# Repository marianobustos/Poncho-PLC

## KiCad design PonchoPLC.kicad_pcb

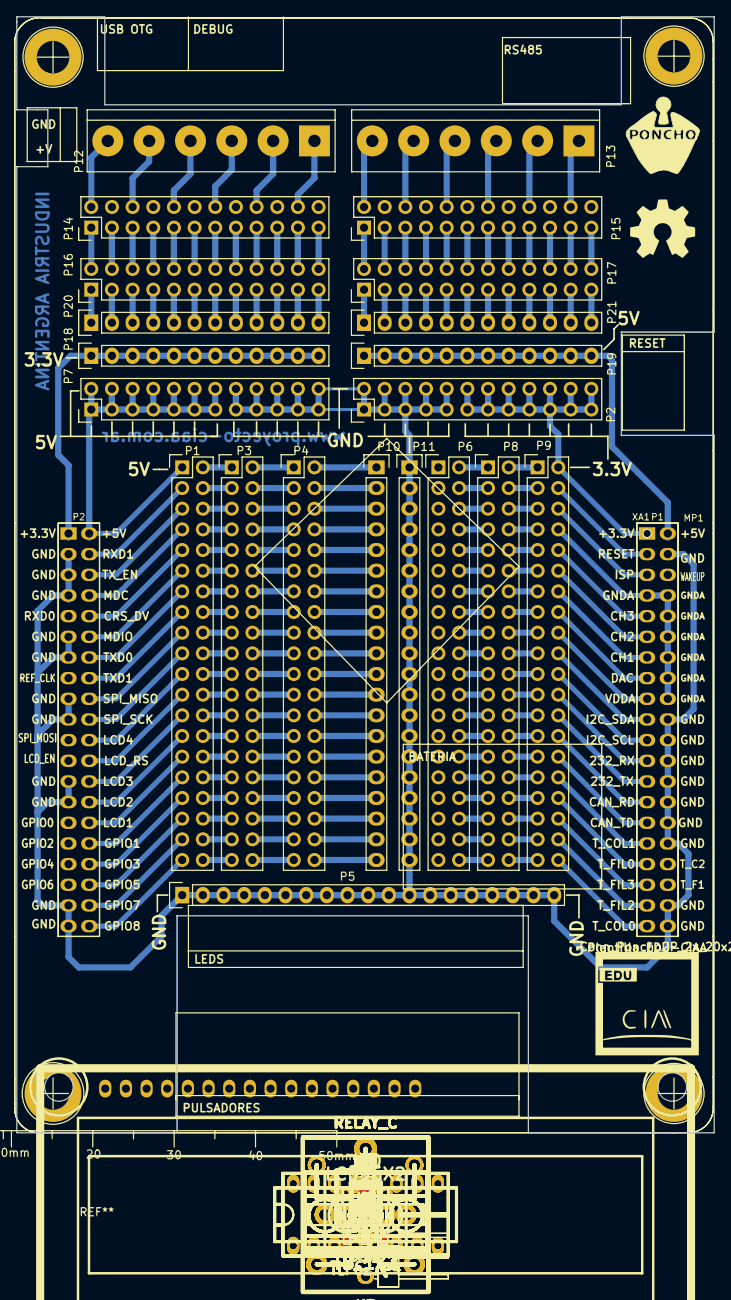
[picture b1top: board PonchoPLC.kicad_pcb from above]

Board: 2 copper layers, 85.7 x 137.2 mm, 135 parts (0 on the bottom side), 253 nets.

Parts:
C1, C2, C3, C4: 100nF; C_1206
C5, C6, C7, C8: 1uF; C_1206
D1, D2, D3, D4, D5, D6, D7, D8, D9, D10, D11, D12, D13, D16, D17: LED red; LED_1206
D14, D15, D18, D19: LL4148; SOD80C
DS1: LCD16X2; LCD_16x2
G101: Logo_OSHWA
J1: I2C; HEADER-4H
J2: RS-232; HEADER-4H
J3, J4, J8, J9, J10, J11: TB_1X3; BORNERA3
J5: TB_1X2; BORNERA2
J6, J7: TB_1X2; BORNERA3
JP1, JP2, JP3, JP4: Jumper; Pin_strip_2
K1, K2, K3, K4: RELAY_C; Relay_C
MP1: Plantilla_EDU-CIAA
P1, P3, P4, P6, P8, P9: CONN_02X20; Pin_Header_Straight_2x20
P2, P7: CONN_01X20; Pin_Header_Straight_2x12
P5: CONN_01X19; Pin_Header_Straight_1x19
P10, P11: CONN_01X20; Pin_Header_Straight_1x20
P12, P13: CONN_01X06; bornier6
P14, P15, P16, P17: CONN_02X12; Pin_Header_Straight_2x12
P18, P19, P20, P21: CONN_01X12; Pin_Header_Straight_1x12
Q1, Q2, Q3, Q4: FQT13N06L; SOT-223
Q5, Q6, Q7, Q8: 2N7002; SOT23
R1: 100; R_1206
R2, R3, R4, R5, R6, R7, R8: 3.3k; R_1206
R9, R10, R11, R12, R13, R14, R15: 4.7k; R_1206
R16, R18, R20, R22, R24, R26, R28: 2.2k; R_1206
R17, R19, R21, R23, R25, R27, R29, R30, R31, R32, R33, R38, R39, R42, R43: 100k; R_1206
R34, R35, R36, R37, R40, R41, R44, R45: 330; R_1206
RV1: 10K; TRIMER_V
TH1, TH2, TH3, TH4: PTS12066V100; PTC_1210
U1, U2: TLP627-4; DIP_16-300_socket
U3, U4, U5, U6: MCP1416; SOT-23-5
XA1: Conn_Poncho2P_2x_20x2; poncho_grande

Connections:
+3.3V: P2.11, P2.12, P2.13, P2.14, P2.15, P2.16, P2.17, P2.18, P2.19, P2.20, P2.21, P2.22, P2.23, P2.24, P9.2
+3.3VADC: P9.18, XA1.17
+3.3VP: P18.1, P18.2, P18.3, P18.4, P18.5, P18.6, P18.7, P18.8, P18.9, P18.10, P18.11, P18.12, XA1.41
+3V3: J1.1, J2.1, R16.2, R17.2, R18.2, R19.2, R20.2, R21.2, R22.2, R23.2, R24.2, R25.2, R26.2, R27.2, R28.2, R29.2, XA1.1
+5V: C1.2, C2.2, C3.2, C4.2, C5.2, C6.2, C7.2, C8.2, D12.1, D13.1, D14.2, D15.2, D16.1, D17.1, D18.2, D19.2, DS1.2, DS1.15, K1.5, K2.5, K3.5, K4.5, P19.1, P19.2, P19.3, P19.4, P19.5, P19.6, P19.7, P19.8, P19.9, P19.10, P19.11, P19.12, RV1.1, U3.2, U4.2, U5.2, U6.2, XA1.2
+5VP: P1.1, P7.1, P7.2, P7.3, P7.4, P7.5, P7.6, P7.7, P7.8, P7.9, P7.10, P7.11, P7.12, P7.13, P7.14, XA1.42
/Conector del Poncho/COL0: D1.2, R17.1, U1.16, XA1.39
/Conector del Poncho/COL1: D2.2, R19.1, U1.14, XA1.31
/Conector del Poncho/COL2: D3.2, R21.1, U1.12, XA1.34
/Conector del Poncho/LCD1: DS1.11, XA1.70
/Conector del Poncho/LCD2: DS1.12, XA1.68
/Conector del Poncho/LCD3: DS1.13, XA1.66
/Conector del Poncho/LCD4: DS1.14, XA1.62
/Conector del Poncho/LCD_EN: DS1.6, XA1.63
/Conector del Poncho/RS: DS1.4, XA1.64
/Conector del Poncho/RXD: J2.2, XA1.23
/Conector del Poncho/SCL: J1.3, XA1.21
/Conector del Poncho/SDA: J1.2, XA1.19
/Conector del Poncho/TXD: J2.3, XA1.25
/Entradas Optoacopladas/COM: J5.2, R9.1, R10.1, R11.1, R12.1, R13.1, R14.1, R15.1, U1.2, U1.4, U1.6, U1.8, U2.2, U2.4, U2.6
/Entradas Optoacopladas/DIN3: D4.2, R23.1, U1.10, XA1.33
/Entradas Optoacopladas/DIN4: D5.2, R25.1, U2.16, XA1.36
/Entradas Optoacopladas/DIN5: D6.2, R27.1, U2.14, XA1.37
/Entradas Optoacopladas/DIN6: D7.2, R29.1, U2.12, XA1.35
/Entradas Optoacopladas/IN0: J3.1, R2.1
/Entradas Optoacopladas/IN1: J3.2, R3.1
/Entradas Optoacopladas/IN2: J3.3, R4.1
/Entradas Optoacopladas/IN3: J4.1, R5.1
/Entradas Optoacopladas/IN4: J4.2, R6.1
/Entradas Optoacopladas/IN5: J4.3, R7.1
/Entradas Optoacopladas/IN6: J5.1, R8.1
/Salidas Digitales/C1A: J8.3, K2.1
/Salidas Digitales/C1B: J9.3, K4.1
/Salidas Digitales/C1C: J10.3, K1.1
/Salidas Digitales/C1D: J11.3, K3.1
/Salidas Digitales/DOUT0: Q6.1, R39.1, XA1.69
/Salidas Digitales/DOUT1: Q8.1, R43.1, XA1.72
/Salidas Digitales/DOUT2: Q5.1, R38.1, XA1.71
/Salidas Digitales/DOUT3: Q7.1, R42.1, XA1.74
/Salidas Digitales/DOUT4: JP2.1, R30.1, U3.3, XA1.73
/Salidas Digitales/DOUT5: JP1.1, R31.1, U4.3, XA1.76
/Salidas Digitales/DOUT6: JP3.1, R32.1, U5.3, XA1.75
/Salidas Digitales/DOUT7: JP4.1, R33.1, U6.3, XA1.78
/Salidas Digitales/MOS4: JP2.2, Q1.1, R34.2, U3.5
/Salidas Digitales/MOS5: JP1.2, Q2.1, R35.2, U4.5
/Salidas Digitales/MOS6: JP3.2, Q3.1, R36.2, U5.5
/Salidas Digitales/MOS7: JP4.2, Q4.1, R37.2, U6.5
/Salidas Digitales/NC1A: J8.1, K2.4
/Salidas Digitales/NC1B: J9.1, K4.4
/Salidas Digitales/NC1C: J10.1, K1.4
/Salidas Digitales/NC1D: J11.1, K3.4
/Salidas Digitales/NO1A: J8.2, K2.3
/Salidas Digitales/NO1B: J9.2, K4.3
/Salidas Digitales/NO1C: J10.2, K1.3
/Salidas Digitales/NO1D: J11.2, K3.3
GND: C1.1, C2.1, C3.1, C4.1, C5.1, C6.1, C7.1, C8.1, D8.2, D9.2, D10.2, D11.2, DS1.1, DS1.5, J1.4, J2.4, P2.1, P2.2, P2.3, P2.4, P2.5, P2.6, P2.7, P2.8, P2.9, P2.10, P5.1, P5.2, P5.3, P5.4, P5.5, P5.6, P5.7, P5.8, P5.9, P5.10, P5.11, P5.12, P5.13, P5.14, P5.15, P5.16, P5.17, P5.18, P5.19, P7.15, P7.16, P7.17, P7.18, P7.19, P7.20, P7.21, P7.22, P7.23, P7.24, P11.1, P11.2, P11.3, P11.4, P11.5, P11.6, P11.7, P11.8, P11.9, P11.10, P11.11, P11.12, P11.13, P11.14, P11.15, P11.16, P11.17, P11.18, P11.19, P11.20, Q1.3, Q2.3, Q3.3, Q4.3, Q5.3, Q6.3, Q7.3, Q8.3, R1.2, R30.2, R31.2, R32.2, R33.2, R38.2, R39.2, R42.2, R43.2, RV1.3, U1.9, U1.11, U1.13, U1.15, U2.11, U2.13, U2.15, U3.4, U4.4, U5.4, U6.4, XA1.4, XA1.20, XA1.22, XA1.24, XA1.26, XA1.28, XA1.30, XA1.32, XA1.38, XA1.40, XA1.43, XA1.45, XA1.47, XA1.51, XA1.53, XA1.57, XA1.59, XA1.65, XA1.67, XA1.77, XA1.79
GNDA: P9.8, XA1.7, XA1.8, XA1.10, XA1.12, XA1.14, XA1.16, XA1.18
unnamed: D1.1, R16.1
unnamed: D2.1, R18.1
unnamed: D3.1, R20.1
unnamed: D4.1, R22.1
unnamed: D5.1, R24.1
unnamed: D6.1, R26.1
unnamed: D7.1, R28.1
unnamed: D8.1, R37.1
unnamed: D9.1, R34.1
unnamed: D10.1, R35.1
unnamed: D11.1, R36.1
unnamed: D12.2, R40.2
unnamed: D13.2, R41.2
unnamed: D14.1, K1.2, Q5.2, R40.1
unnamed: D15.1, K2.2, Q6.2, R41.1
unnamed: D16.2, R44.2
unnamed: D17.2, R45.2
unnamed: D18.1, K3.2, Q7.2, R44.1
unnamed: D19.1, K4.2, Q8.2, R45.1
unnamed: DS1.3, RV1.2
unnamed: DS1.16, R1.1
unnamed: J6.1, TH1.2
unnamed: J6.2, TH2.2
unnamed: J7.1, TH3.2
unnamed: J7.2, TH4.2
unnamed: P1.2, P3.1
unnamed: P1.4, P3.3
unnamed: P1.6, P3.5
unnamed: P1.8, P3.7
unnamed: P1.10, P3.9
unnamed: P1.12, P3.11
unnamed: P1.14, P3.13
unnamed: P1.16, P3.15
unnamed: P1.18, P3.17
unnamed: P1.20, P3.19
unnamed: P1.22, P3.21
unnamed: P1.24, P3.23
unnamed: P1.26, P3.25
unnamed: P1.28, P3.27
unnamed: P1.30, P3.29
unnamed: P1.32, P3.31
unnamed: P1.34, P3.33
unnamed: P1.36, P3.35
unnamed: P1.38, P3.37
unnamed: P1.40, P3.39
unnamed: P3.2, P4.1
unnamed: P3.4, P4.3
unnamed: P3.6, P4.5
unnamed: P3.8, P4.7
unnamed: P3.10, P4.9
unnamed: P3.12, P4.11
unnamed: P3.14, P4.13
unnamed: P3.16, P4.15
unnamed: P3.18, P4.17
unnamed: P3.20, P4.19
unnamed: P3.22, P4.21
unnamed: P3.24, P4.23
unnamed: P3.26, P4.25
unnamed: P3.28, P4.27
unnamed: P3.30, P4.29
unnamed: P3.32, P4.31
unnamed: P3.34, P4.33
unnamed: P3.36, P4.35
unnamed: P3.38, P4.37
unnamed: P3.40, P4.39
unnamed: P6.2, P8.1
unnamed: P6.4, P8.3
unnamed: P6.6, P8.5
unnamed: P6.8, P8.7
unnamed: P6.10, P8.9
unnamed: P6.12, P8.11
unnamed: P6.14, P8.13
unnamed: P6.16, P8.15
unnamed: P6.18, P8.17
unnamed: P6.20, P8.19
unnamed: P6.22, P8.21
unnamed: P6.24, P8.23
unnamed: P6.26, P8.25
unnamed: P6.28, P8.27
unnamed: P6.30, P8.29
unnamed: P6.32, P8.31
unnamed: P6.34, P8.33
unnamed: P6.36, P8.35
unnamed: P6.38, P8.37
unnamed: P6.40, P8.39
unnamed: P8.2, P9.1
unnamed: P8.4, P9.3
unnamed: P8.6, P9.5
unnamed: P8.8, P9.7
unnamed: P8.10, P9.9
unnamed: P8.12, P9.11
unnamed: P8.14, P9.13
unnamed: P8.16, P9.15
unnamed: P8.18, P9.17
unnamed: P8.20, P9.19
unnamed: P8.22, P9.21
unnamed: P8.24, P9.23
unnamed: P8.26, P9.25
unnamed: P8.28, P9.27
unnamed: P8.30, P9.29
unnamed: P8.32, P9.31
unnamed: P8.34, P9.33
unnamed: P8.36, P9.35
unnamed: P8.38, P9.37
unnamed: P8.40, P9.39
unnamed: P4.2, P10.1
unnamed: P4.4, P10.2
unnamed: P4.6, P10.3
unnamed: P4.8, P10.4
unnamed: P4.10, P10.5
unnamed: P4.12, P10.6
unnamed: P4.14, P10.7
unnamed: P4.16, P10.8
unnamed: P4.18, P10.9
unnamed: P4.20, P10.10
unnamed: P4.22, P10.11
unnamed: P4.24, P10.12
unnamed: P4.26, P10.13
unnamed: P4.28, P10.14
unnamed: P4.30, P10.15
unnamed: P4.32, P10.16
unnamed: P4.34, P10.17
unnamed: P4.36, P10.18
unnamed: P4.38, P10.19
unnamed: P4.40, P10.20
unnamed: P12.1, P14.22
unnamed: P12.2, P14.18
unnamed: P12.3, P14.14
unnamed: P12.4, P14.10
unnamed: P12.5, P14.6
unnamed: P12.6, P14.2
unnamed: P13.1, P15.22
unnamed: P13.2, P15.18
unnamed: P13.3, P15.14
unnamed: P13.4, P15.10
unnamed: P13.5, P15.6
unnamed: P13.6, P15.2
unnamed: P14.1, P16.2
unnamed: P14.3, P16.4
unnamed: P14.5, P16.6
unnamed: P14.7, P16.8
unnamed: P14.9, P16.10
unnamed: P14.11, P16.12
unnamed: P14.13, P16.14
unnamed: P14.15, P16.16
unnamed: P14.17, P16.18
unnamed: P14.19, P16.20
unnamed: P14.21, P16.22
unnamed: P14.23, P16.24
unnamed: P15.1, P17.2
unnamed: P15.3, P17.4
unnamed: P15.5, P17.6
unnamed: P15.7, P17.8
unnamed: P15.9, P17.10
unnamed: P15.11, P17.12
unnamed: P15.13, P17.14
unnamed: P15.15, P17.16
unnamed: P15.17, P17.18
unnamed: P15.19, P17.20
unnamed: P15.21, P17.22
unnamed: P15.23, P17.24
unnamed: P16.1, P20.1
unnamed: P16.3, P20.2
unnamed: P16.5, P20.3
unnamed: P16.7, P20.4
unnamed: P16.9, P20.5
unnamed: P16.11, P20.6
unnamed: P16.13, P20.7
unnamed: P16.15, P20.8
unnamed: P16.17, P20.9
unnamed: P16.19, P20.10
unnamed: P16.21, P20.11
unnamed: P16.23, P20.12
unnamed: P17.1, P21.1
unnamed: P17.3, P21.2
unnamed: P17.5, P21.3
unnamed: P17.7, P21.4
unnamed: P17.9, P21.5
unnamed: P17.11, P21.6
unnamed: P17.13, P21.7
unnamed: P17.15, P21.8
unnamed: P17.17, P21.9
unnamed: P17.19, P21.10
unnamed: P17.21, P21.11
unnamed: P17.23, P21.12
unnamed: Q1.2, Q1.4, TH1.1
unnamed: Q2.2, Q2.4, TH2.1
unnamed: Q3.2, Q3.4, TH3.1
unnamed: Q4.2, Q4.4, TH4.1
unnamed: R2.2, R9.2, U1.1
unnamed: R3.2, R10.2, U1.3
unnamed: R4.2, R11.2, U1.5
unnamed: R5.2, R12.2, U1.7
unnamed: R6.2, R13.2, U2.1
unnamed: R7.2, R14.2, U2.3
unnamed: R8.2, R15.2, U2.5

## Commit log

2016-03-08 :octocat: Added .gitattributes
2016-03-08 Versión Inicial del proyecto
    Primer versión del diseño.
2016-03-08 Modificación de rutas
    Cambio de la barra de las rutas de los directorios, / en vez de \. para
    lograr compatibilidad con linux.
2016-07-10 Librería de footprint del proyecto
    Generación de la librería de footprint propia del proyecto.
